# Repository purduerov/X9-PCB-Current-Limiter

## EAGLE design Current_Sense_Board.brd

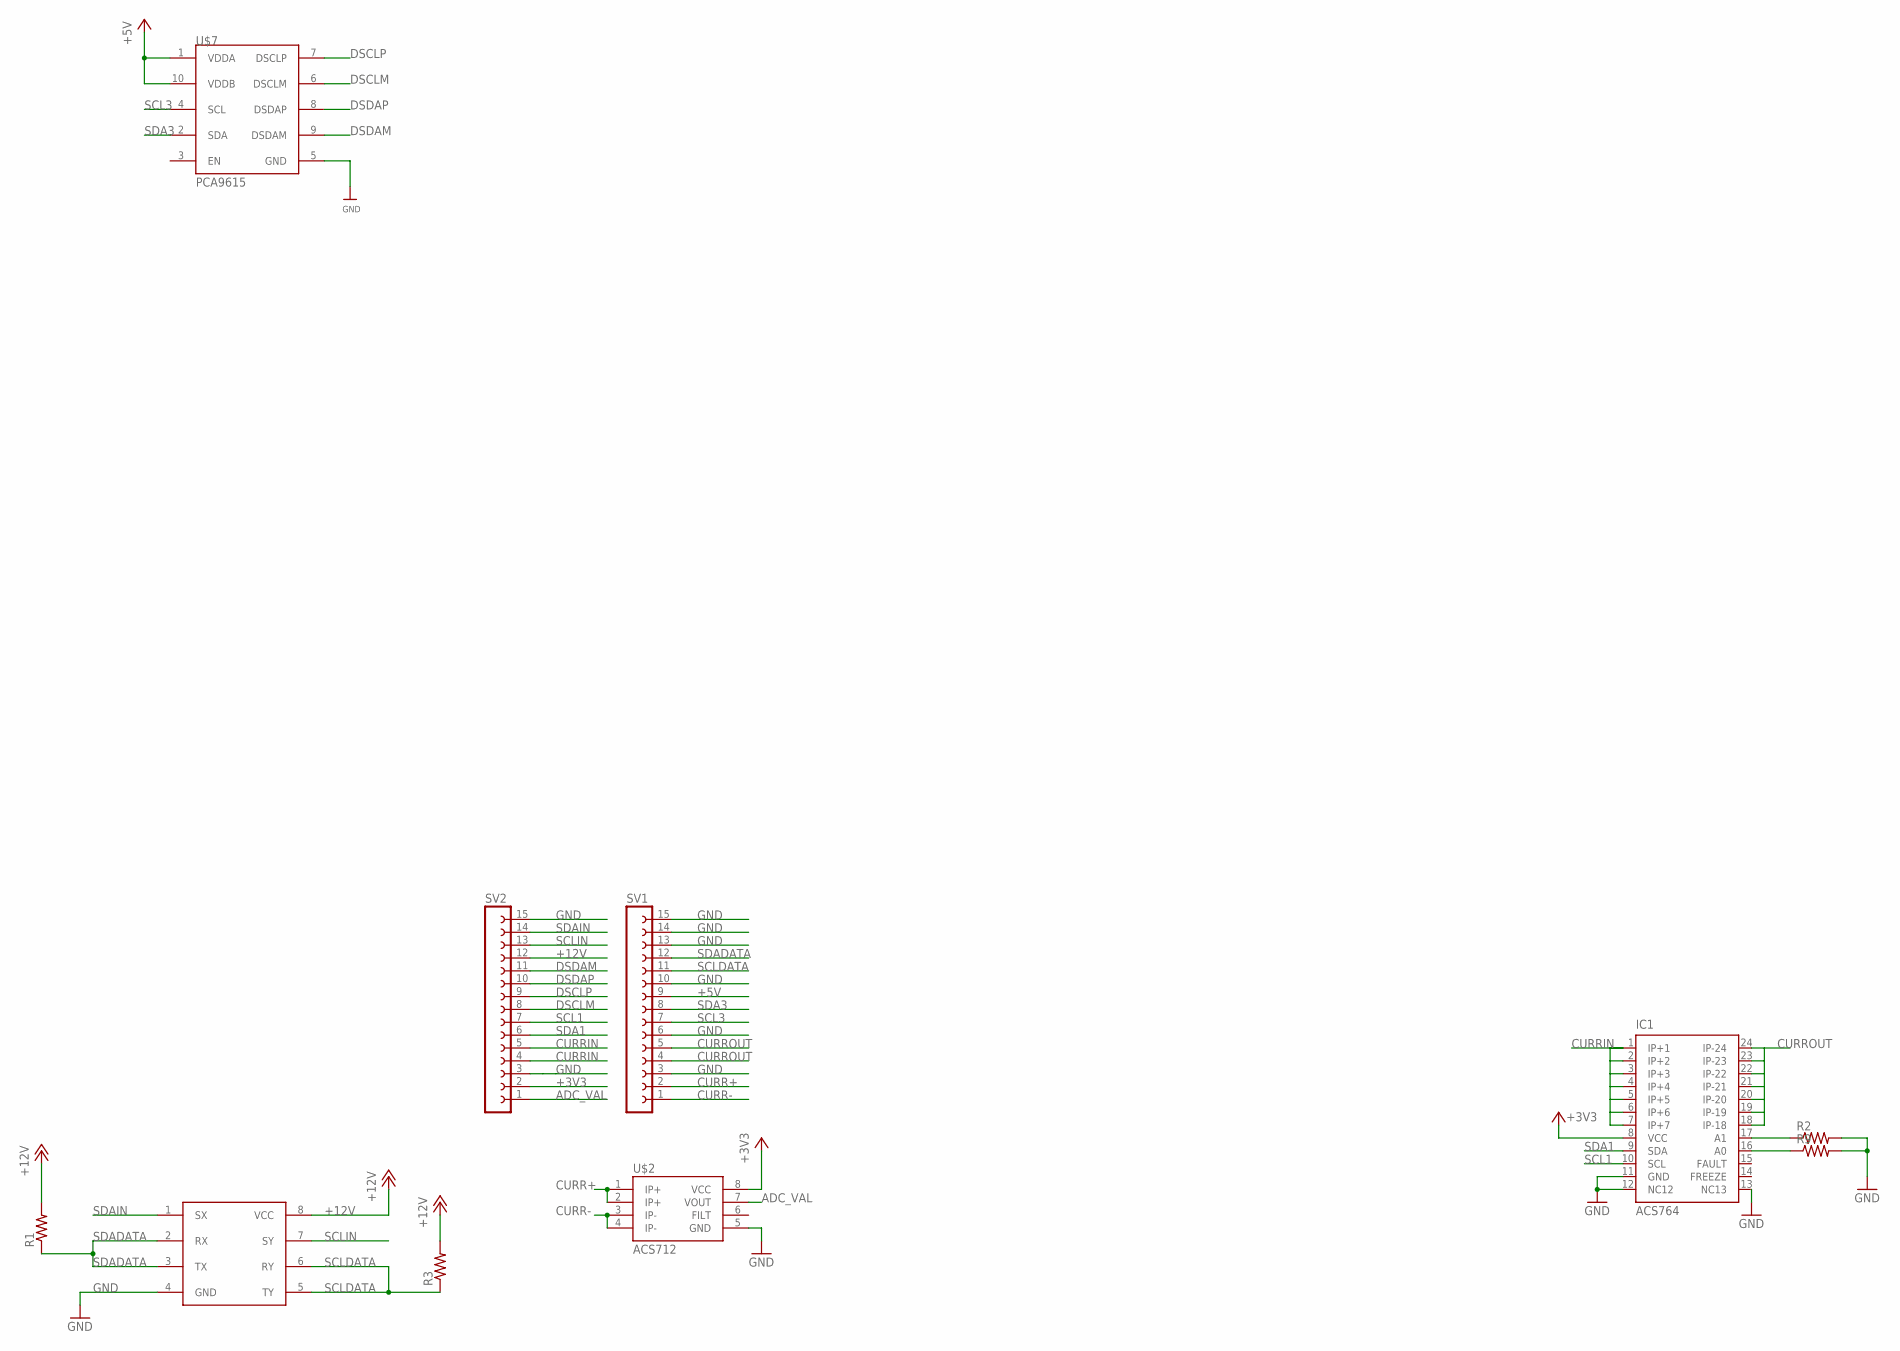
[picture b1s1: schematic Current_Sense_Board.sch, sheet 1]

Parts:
IC1: ACS764; SSOP24
R1, R2, R3, R9: RESISTOR0603; 0603-RES
SV1, SV2: FE15-1; FE15
U$1: PCA9000; TSSOP8
U$2: ACS712; SO08
U$7: PCA9615; MSOP_10

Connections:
+3V3: IC1.8 (VCC), SV2.2, U$2.8 (VCC)
+5V: SV1.9, U$7.1 (VDDA), U$7.10 (VDDB)
+12V: R1.2, R3.2, SV2.12, U$1.8 (VCC)
ADC_VAL: SV2.1, U$2.7 (VOUT)
CURR+: SV1.2, U$2.1 (IP+), U$2.2 (IP+)
CURR-: SV1.1, U$2.3 (IP-), U$2.4 (IP-)
CURRIN: IC1.1 (IP+1), IC1.2 (IP+2), IC1.3 (IP+3), IC1.4 (IP+4), IC1.5 (IP+5), IC1.6 (IP+6), IC1.7 (IP+7), SV2.4, SV2.5
CURROUT: IC1.18 (IP-18), IC1.19 (IP-19), IC1.20 (IP-20), IC1.21 (IP-21), IC1.22 (IP-22), IC1.23 (IP-23), IC1.24 (IP-24), SV1.4, SV1.5
DSCLM: SV2.8, U$7.6 (DSCLM)
DSCLP: SV2.9, U$7.7 (DSCLP)
DSDAM: SV2.11, U$7.9 (DSDAM)
DSDAP: SV2.10, U$7.8 (DSDAP)
GND: IC1.11 (GND), IC1.12 (NC12), IC1.13 (NC13), R2.2, R9.2, SV1.3, SV1.6, SV1.10, SV1.13, SV1.14, SV1.15, SV2.3, SV2.15, U$1.4 (GND), U$2.5 (GND), U$7.5 (GND)
unnamed: IC1.17 (A1), R2.1
unnamed: IC1.16 (A0), R9.1
SCL1: IC1.10 (SCL), SV2.7
SCL3: SV1.7, U$7.4 (SCL)
SCLDATA: R3.1, SV1.11, U$1.5 (TY), U$1.6 (RY)
SCLIN: SV2.13, U$1.7 (SY)
SDA1: IC1.9 (SDA), SV2.6
SDA3: SV1.8, U$7.2 (SDA)
SDADATA: R1.1, SV1.12, U$1.2 (RX), U$1.3 (TX)
SDAIN: SV2.14, U$1.1 (SX)

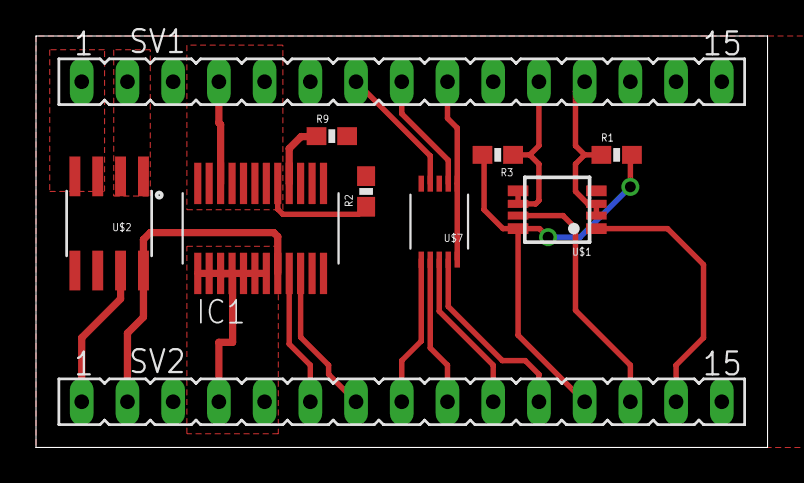
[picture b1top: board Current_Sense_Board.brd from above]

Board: 2 copper layers, 40.6 x 22.9 mm, 10 parts (0 on the bottom side), 23 nets.

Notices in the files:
parts and their libraries:
SparkFun-AnalogIC: Licensing:Creative Commons ShareAlike 4.0 International - https://creativecommons.org/licenses/by-sa/4.0
